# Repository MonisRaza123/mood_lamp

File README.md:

# mood_lamp

‘Mood Lamp’ as the name suggests, enables its user to lighten their room with the colour of their liking. The lamp has two modes of operation-
1. Manually changing the red, blue, and green intensities by turning the knobs provided on the enclosure.
1. Contact-less control using an android app using Bluetooth as the technology for wireless communication.

ESP32 WROOM is used as the microcontroller with 3W RGB LEDs being the illuminant driven by a constant current driving circuit.

## Six Box Model

Every embedded system can be categorised into the following six blocks of operation:

In order to break down our device into these basic building blocks, let's list down the requirements of our device:

- An input mechanism to vary the R, G, B intensities manually.
- A wireless methodology to vary the R, G, B intensities from a distance.
- An LED panel serves as the output of our system.
-  A microcontroller to generate PWM signals controlling the LED circuit.
-  A constant current circuit to drive the LEDs.
-   A supply to power the whole circuit.
-   An enclosure to contain the entire circuitry and be the lamp's body.

1. **INPUTS**: The manual input by turning the knobs is realised by using three 100k panel mount potentiometers whose values are read by the ADC of the microcontroller. In the wireless mode, the inputs are received by the Bluetooth module integrated into the microcontroller and sent by an android app. There is also another input given by a rocker switch deciding the mode of operation of the lamp.
2. **OUTPUT**: The output of the system is represented by the three 3W RGB SMD LEDs located on the LED panel lighting up the lamp. There is also a power-on LED indicating whether the system is connected to a power source or not.
3. **MICROCONTROLLER**: ESP32-WROOM is the microcontroller of choice as it has multiple PWM channels and is integrated with Bluetooth and WiFi capabilities.
4. **POWER SUPPLY**: A 12V-2A DC adapter is used to give raw 12V which supplies the necessary bias to light up the LED panel. Since the microcontroller operates as 3.3V, LM2576 adjustable buck converter is used to provide the necessary voltage levels.
5. **COMMUNICATIONS**: An FTDI programmer is used to download the code from the IDE. A six-pin connector is added to the control board, this makes programming the microcontroller repeatedly a much easier task.

## Project Description

### Block Diagram

### Hardware Description
The hardware of this project consists of two boards:
1. LED Panel: The board for LEDs is separate from the rest of the
  circuitry as they consist of high wattage elements which should be
  isolated to avoid unwanted transfer of heat to other components
  such as the microcontroller.
2. Control circuit: It consists of the microcontroller ESP32, the power
  supply block consisting of a DC barrel jack and the buck converter
  circuit. It also hosts the constant current driving circuit consisting
  of NPN transistors (MJE3055T), diodes (1N4007), and the accom-
  panying resistors for biasing and setting the current to comply
  with the LED specifications and power ratings of the transistors.
  There are heat sinks for the transistors and the buck converter to
  take away excess heat to improve device performance and extend
  its life.

**Wondering how the current is kept constant?**

Let’s start with the collector current equation giving us insight into what controls the
current through the load.

It is apparent that Ic is exponentially dependent on Vbe. Observe that if the current through the load increases, the voltage drop across Re also increases thereby decreasing Vbe which eventually decreases Ic. This corrective action occurs because the voltage appearing at the base is kept constant by the voltage reference set by the diodes.
Thus the current Ic is kept relatively constant even if the voltage across the load changes.
Now the question arises as to how the intensity of LEDs is varied using the microcontroller. The answer is PWM.

### Software Description
The program for this project is written and compiled on Arduino IDE. The following flowchart explains the logic of code:

## Circuit Design

### LED Panel
|  || 
|:--:| :--:|
| *schematic* |                                                                          *board layout*|

### Control Board
||
|:--:|
|*schematic*|

||
|:--:|
|*board layout*|

## Fabricated PCB

|||
|:--:| :--:|
|*Control circuit PCB*|*LED panel PCB*|

## END RESULT

| |
|:--:|
||
|*Enclosed lamp from different angles*|

| |
|:--:|
||
||
|*Mood Lamp showing different shades.*|

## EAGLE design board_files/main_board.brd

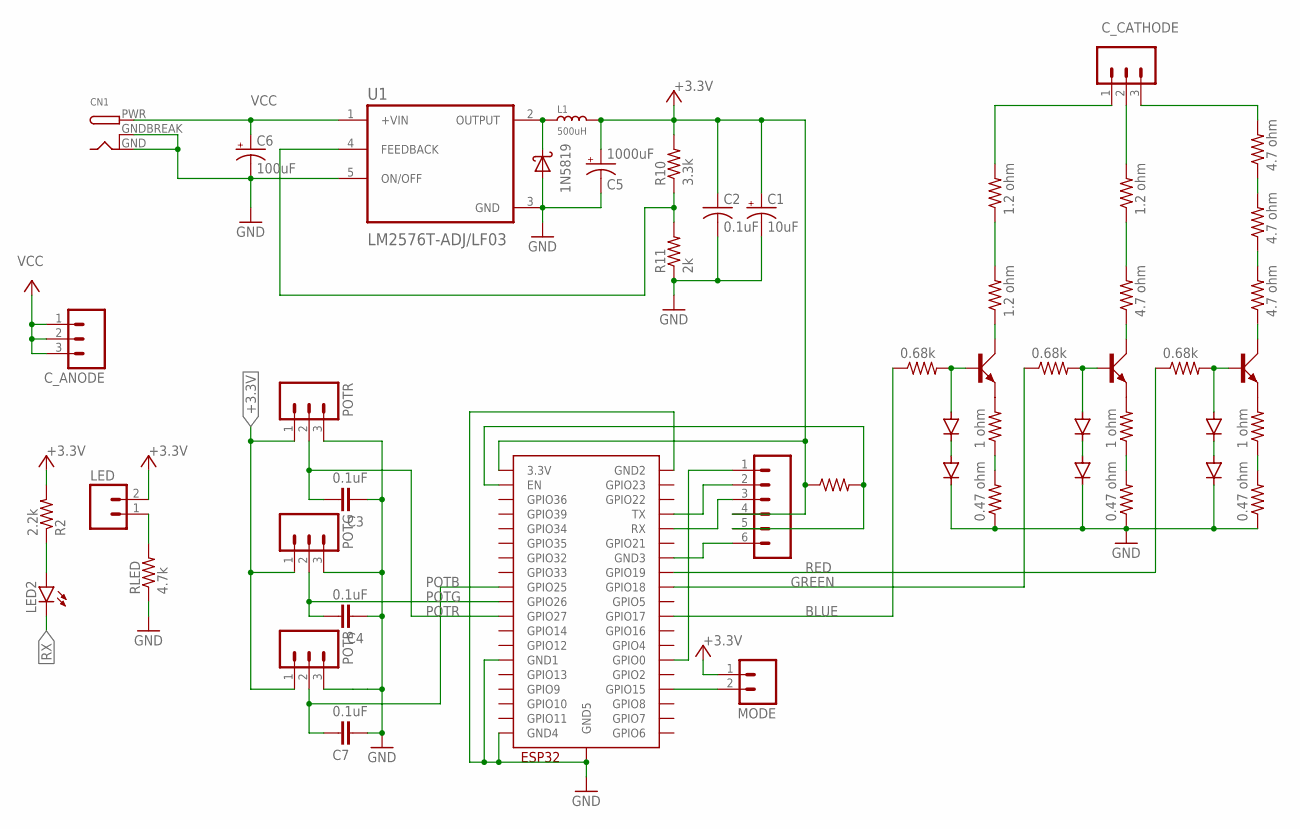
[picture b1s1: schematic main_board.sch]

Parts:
C1: 10uF; B/3528-21R
C2: 0.1uF; C0603
C3, C4, C7: 0.1uF; C2.5-3
C5: 1000uF; E3,5-8
C6: 100uF; E3,5-8
CN1: DCBARRELPTH; DCJACK_2MM_PTH
C_ANODE: M03; 03P
C_CATHODE: M03; 03P
D11: 1N5819; DO41-10
DB1, DB2: 1N4004; DO41-10
DG1, DG2: 1N4004; DO41-10
DR1, DR2: 1N4004; DO41-10
ESP32_MODULE: ESP32-WROOM
L1: 500uH; INDUCTOR_INT2-3.5-D6.5XH8.0MM
LED: M02; 02P
LED2: LED-RED0603; 0603-RED
MODE: M02; 02P
POTB: M03; 03P
POTG: M03; 03P
POTR: M03; 03P
QB: MJE3055; TO220AV
QG: MJE3055; TO220AV
QR: MJE3055; TO220AV
R1: 10k; R0805
R2: 2.2k; R0805
R10: 3.3k; 0207/7
R11: 2k; 0207/7
RB_B: 0.68k; 0207/7
RB_G: 0.68k; 0207/7
RB_R: 0.68k; 0207/7
RC_B, RC_B1: 1.2 ohm; 0207/15
RC_G: 1.2 ohm; 0207/15
RC_G1: 4.7 ohm; 0207/15
RC_R, RC_R1, RC_R2: 4.7 ohm; 0207/15
RE_B: 1 ohm; 0207/15
RE_B1: 0.47 ohm; 0207/15
RE_G: 1 ohm; 0207/15
RE_G1: 0.47 ohm; 0207/15
RE_R: 1 ohm; 0207/15
RE_R1: 0.47 ohm; 0207/15
RLED: 4.7k; 0207/7
SL2: M06; 06P
U1: LM2576T-ADJ/LF03; TO170P1016X470X2092-5

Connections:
+3.3V: C1.+, C2.1, C5.+, ESP32_MODULE.3V3 (3.3V), L1.2, LED.2, MODE.1, POTB.1, POTG.1, POTR.1, R1.1, R2.2, R10.2, SL2.4
BLUE: ESP32_MODULE.IO17 (GPIO17), RB_B.1
ENABLE: ESP32_MODULE.EN, R1.2, SL2.5
FB: R10.1, R11.2, U1.4 (FEEDBACK)
GND: C1.-, C2.2, C3.1, C4.1, C5.-, C6.-, C7.1, CN1.GND, CN1.GNDBREAK, D11.A, DB2.C, DG2.C, DR2.C, ESP32_MODULE.GND1, ESP32_MODULE.GND2, ESP32_MODULE.GND3, ESP32_MODULE.GND4, ESP32_MODULE.GND5, POTB.3, POTG.3, POTR.3, R11.1, RE_B1.1, RE_G1.1, RE_R1.1, RLED.1, SL2.6, U1.3 (GND), U1.5 (ON/OFF)
GREEN: ESP32_MODULE.IO18 (GPIO18), RB_G.1
MODE: ESP32_MODULE.IO15 (GPIO15), MODE.2
unnamed: DB1.A, QB.B, RB_B.2
unnamed: QB.E, RE_B.2
unnamed: C_CATHODE.3, RC_R.2
unnamed: LED2.A, R2.1
unnamed: QG.E, RE_G.2
unnamed: QR.E, RE_R.2
unnamed: ESP32_MODULE.IO0 (GPIO0), SL2.1
unnamed: C_CATHODE.1, RC_B.2
unnamed: C_CATHODE.2, RC_G.2
unnamed: QB.C, RC_B1.1
unnamed: RE_B.1, RE_B1.2
unnamed: RE_G.1, RE_G1.2
unnamed: RC_G.1, RC_G1.2
unnamed: RE_R.1, RE_R1.2
unnamed: DR1.C, DR2.A
unnamed: DR1.A, QR.B, RB_R.2
unnamed: LED.1, RLED.2
unnamed: DG1.A, QG.B, RB_G.2
unnamed: RC_B.1, RC_B1.2
unnamed: DG1.C, DG2.A
unnamed: RC_R.1, RC_R1.2
unnamed: RC_R1.1, RC_R2.2
unnamed: QG.C, RC_G1.1
unnamed: QR.C, RC_R2.1
unnamed: DB1.C, DB2.A
O/P: D11.C, L1.1, U1.2 (OUTPUT)
POTB: C7.2, ESP32_MODULE.IO25 (GPIO25), POTB.2
POTG: C4.2, ESP32_MODULE.IO26 (GPIO26), POTG.2
POTR: C3.2, ESP32_MODULE.IO27 (GPIO27), POTR.2
RED: ESP32_MODULE.IO19 (GPIO19), RB_R.1
RX: ESP32_MODULE.RX, LED2.C, SL2.3
TX: ESP32_MODULE.TX, SL2.2
VCC: C6.+, CN1.PWR, C_ANODE.1, C_ANODE.2, C_ANODE.3, U1.1 (+VIN)

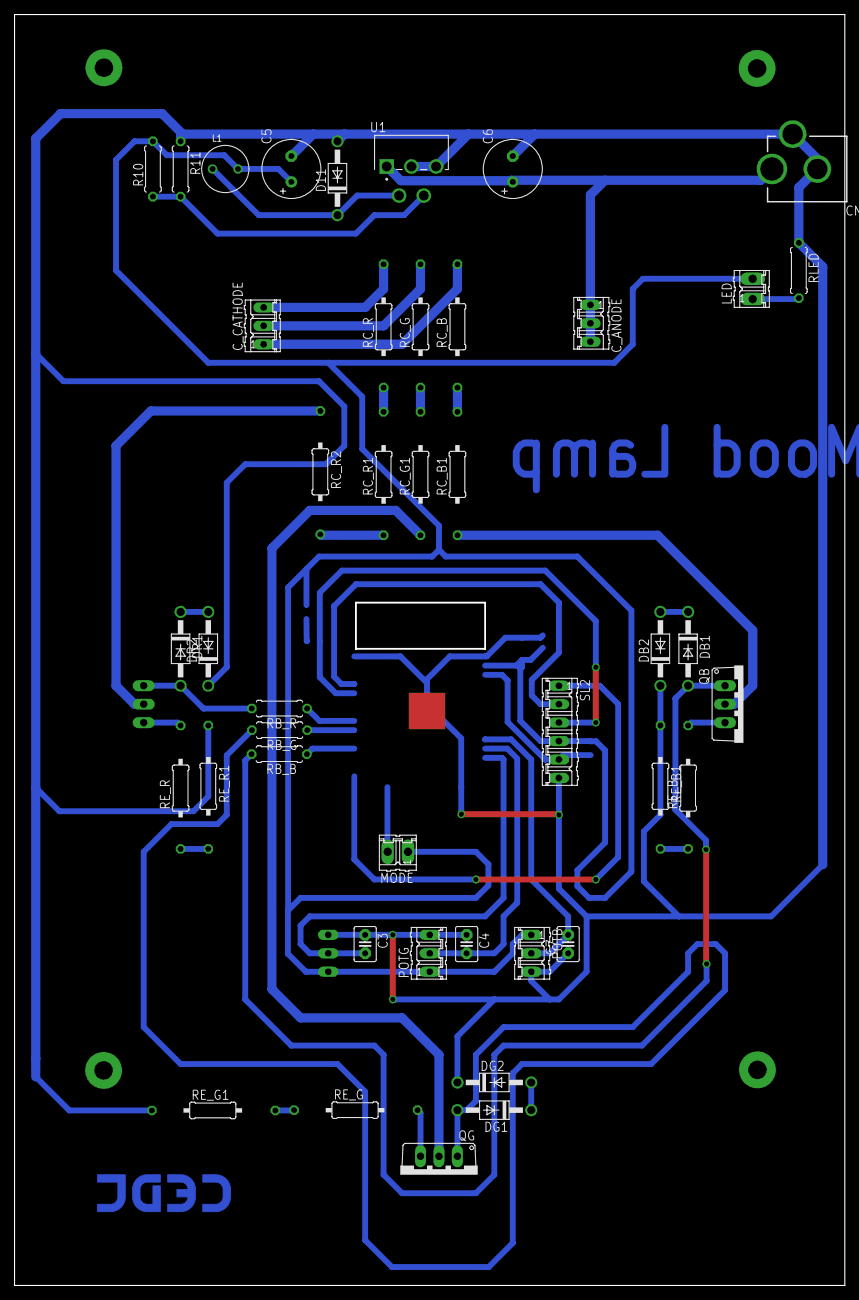
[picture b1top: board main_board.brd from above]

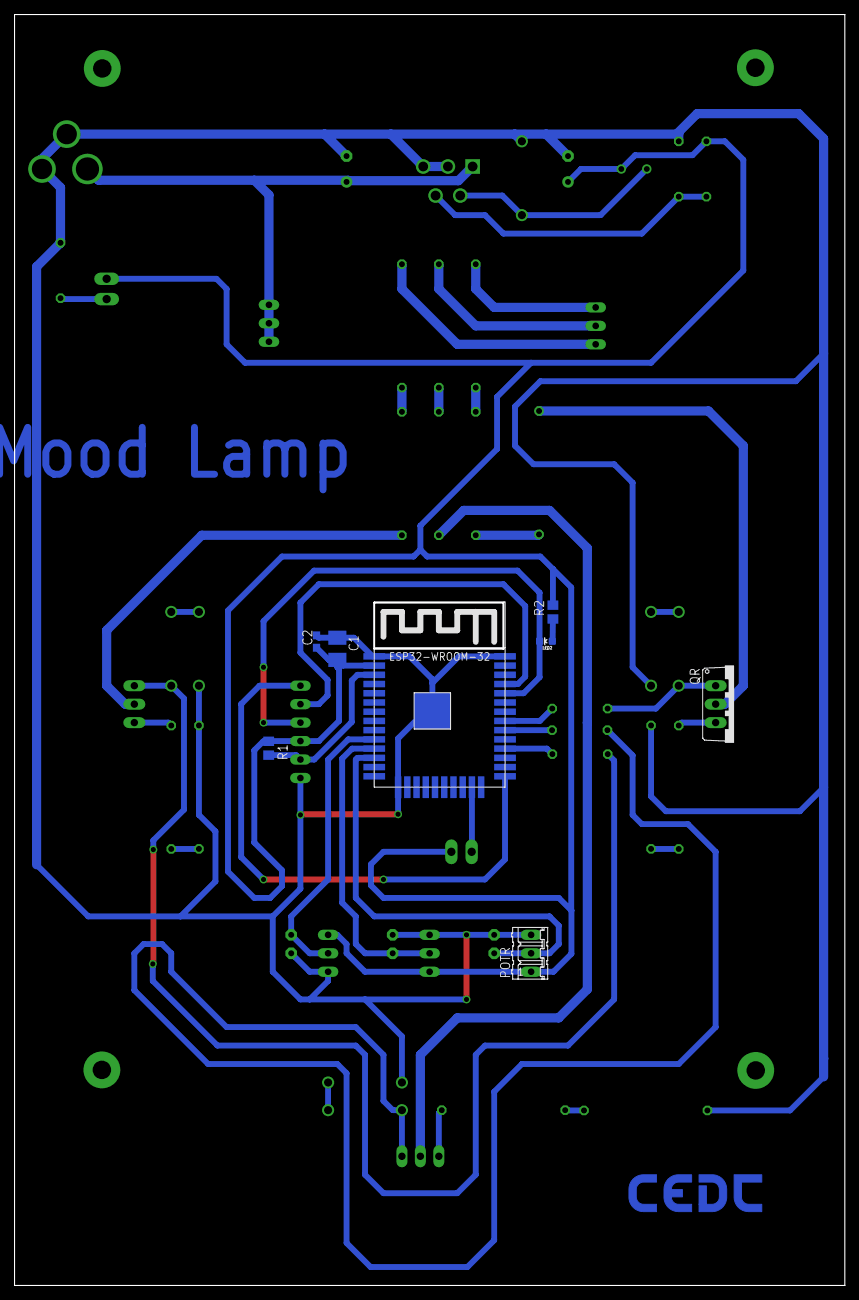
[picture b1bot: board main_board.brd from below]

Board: 2 copper layers, 114.0 x 174.7 mm, 52 parts (8 on the bottom side), 40 nets.

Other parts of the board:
U$1: LOGO-CEDT-BOT-18MM

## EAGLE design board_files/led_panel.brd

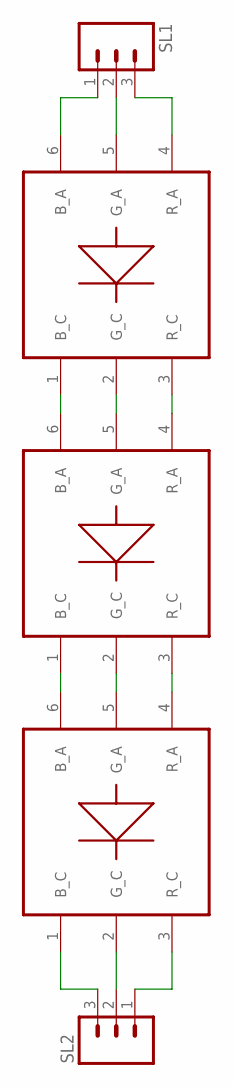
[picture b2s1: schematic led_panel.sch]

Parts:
SL1, SL2: M03; 03P
U$1, U$2, U$3: RGB_SMD_3W; RGB_SMD_6PIN

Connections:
unnamed: SL1.3, U$1.4 (R_A)
unnamed: SL1.1, U$1.6 (B_A)
unnamed: SL2.3, U$3.1 (B_C)
unnamed: SL2.2, U$3.2 (G_C)
unnamed: SL2.1, U$3.3 (R_C)
unnamed: U$1.1 (B_C), U$2.6 (B_A)
unnamed: U$1.2 (G_C), U$2.5 (G_A)
unnamed: U$1.3 (R_C), U$2.4 (R_A)
unnamed: U$2.1 (B_C), U$3.6 (B_A)
unnamed: U$2.2 (G_C), U$3.5 (G_A)
unnamed: U$2.3 (R_C), U$3.4 (R_A)
unnamed: SL1.2, U$1.5 (G_A)

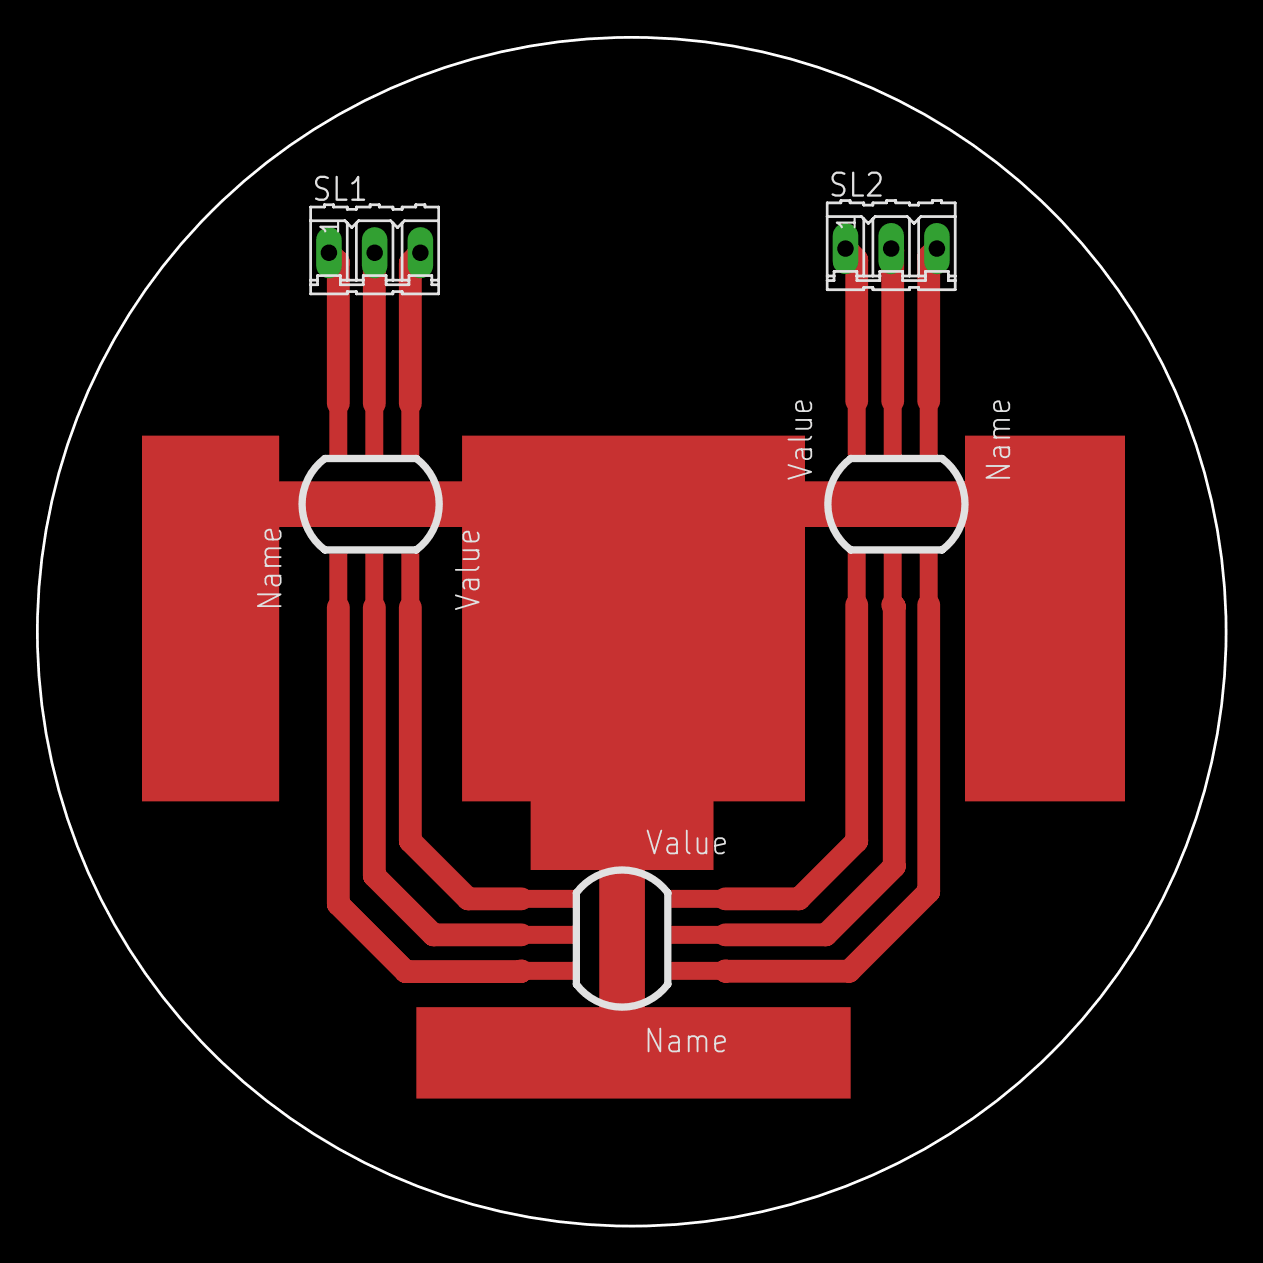
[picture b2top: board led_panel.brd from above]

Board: 2 copper layers, 66.0 x 66.0 mm, 5 parts (0 on the bottom side), 12 nets.

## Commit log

2023-10-06 added report
2023-10-06 renamed image
2023-10-06 rotated images
